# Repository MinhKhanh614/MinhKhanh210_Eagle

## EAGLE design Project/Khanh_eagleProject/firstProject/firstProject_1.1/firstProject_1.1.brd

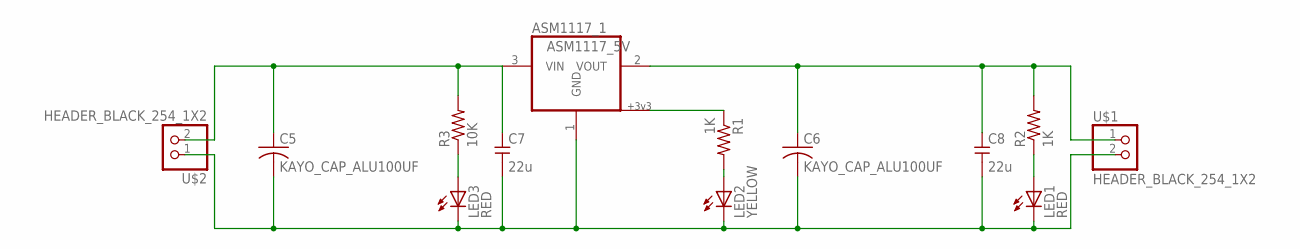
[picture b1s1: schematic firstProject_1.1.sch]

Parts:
ASM1117_1: ASM1117_5V; SOT223
C5, C6: KAYO_CAP_ALU100UF; RCL_PANASONIC_D
C7, C8: 22u; KXN_C0603
LED1, LED3: RED; KXN_LED_0603
LED2: YELLOW; KXN_LED_0603
R1, R2: 1K; R0603_KXN
R3: 10K; R0603_KXN
U$1, U$2: HEADER_BLACK_254_1X2; HEADER_1X2_254

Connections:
GND: ASM1117_1.1 (GND), C5.- (2), C6.- (2), C7.2 (-), C8.2 (-), LED1.C, LED2.C, LED3.C, U$1.2, U$2.1
unnamed: LED3.A, R3.1
unnamed: ASM1117_1.3 (VIN), C5.+ (1), C7.1 (+), R3.2, U$2.2
unnamed: ASM1117_1.2 (VOUT), C6.+ (1), C8.1 (+), R2.2, U$1.1
unnamed: LED2.A, R1.2
unnamed: LED1.A, R2.1
unnamed: ASM1117_1.4, R1.1

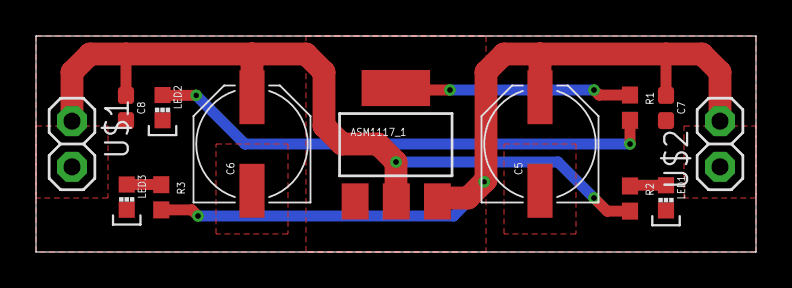
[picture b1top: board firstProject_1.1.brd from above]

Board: 2 copper layers, 40.0 x 12.0 mm, 13 parts (0 on the bottom side), 7 nets.

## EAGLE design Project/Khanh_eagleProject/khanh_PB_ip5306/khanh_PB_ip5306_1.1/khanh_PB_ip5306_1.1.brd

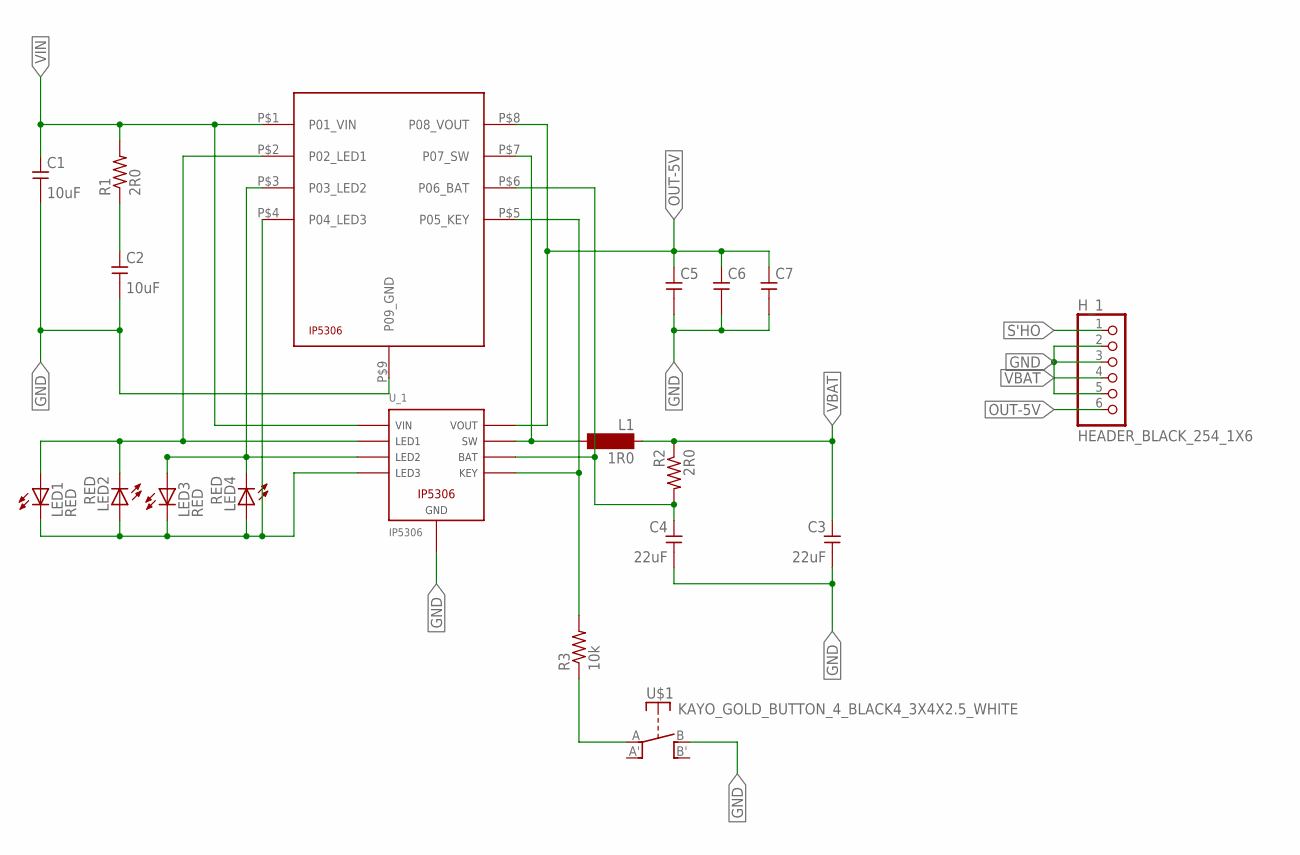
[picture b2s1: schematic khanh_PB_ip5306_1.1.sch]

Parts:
C1, C2: 10uF; C1206
C3, C4: 22uF; C1206
C5, C6, C7: KAYO_CAP_CERAMIC22UF_KXN_0603; KXN_C0603
H_1: HEADER_BLACK_254_1X6; HEADER_1X6_254
L1: 1R0; CKST_0603_0630_PACK
LED1, LED2, LED3, LED4: RED; KXN_LED_0603
R1, R2: 2R0; R0603
R3: 10k; R0603
U$1: KAYO_GOLD_BUTTON_4_BLACK4_3X4X2.5_WHITE; KXN_BUTTON_3_4_2.5MM
U$2: IP5306
U_1: IP5306; ESOP8

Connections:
BAT: C4.1 (+), R2.2, U$2.P$6 (P06_BAT), U_1.6
GND: C1.2 (-), C2.2 (-), C3.2 (-), C4.2 (-), C5.2 (-), C6.2 (-), C7.2 (-), H_1.2, H_1.3, H_1.5, U$1.B, U$2.P$9 (P09_GND), U_1.9
unnamed: C2.1 (+), R1.1
unnamed: R3.1, U$1.A
unnamed: L1.P$2 (2), U$2.P$7 (P07_SW), U_1.7
unnamed: R3.2, U$2.P$5 (P05_KEY), U_1.5
unnamed: LED1.A, LED2.C, U$2.P$2 (P02_LED1), U_1.2
unnamed: LED1.C, LED2.A, LED3.C, LED4.A, U$2.P$4 (P04_LED3), U_1.4
unnamed: LED3.A, LED4.C, U$2.P$3 (P03_LED2), U_1.3
OUT-5V: C5.1 (+), C6.1 (+), C7.1 (+), H_1.6, U$2.P$8 (P08_VOUT), U_1.8
S'HO: H_1.1
VBAT: C3.1 (+), H_1.4, L1.P$1 (1), R2.1
VIN: C1.1 (+), R1.2, U$2.P$1 (P01_VIN), U_1.1

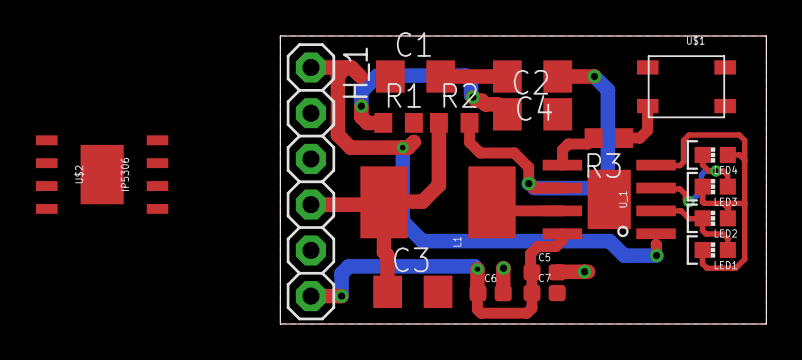
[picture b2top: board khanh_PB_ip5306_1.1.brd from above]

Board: 2 copper layers, 27.0 x 16.0 mm, 19 parts (0 on the bottom side), 12 nets.

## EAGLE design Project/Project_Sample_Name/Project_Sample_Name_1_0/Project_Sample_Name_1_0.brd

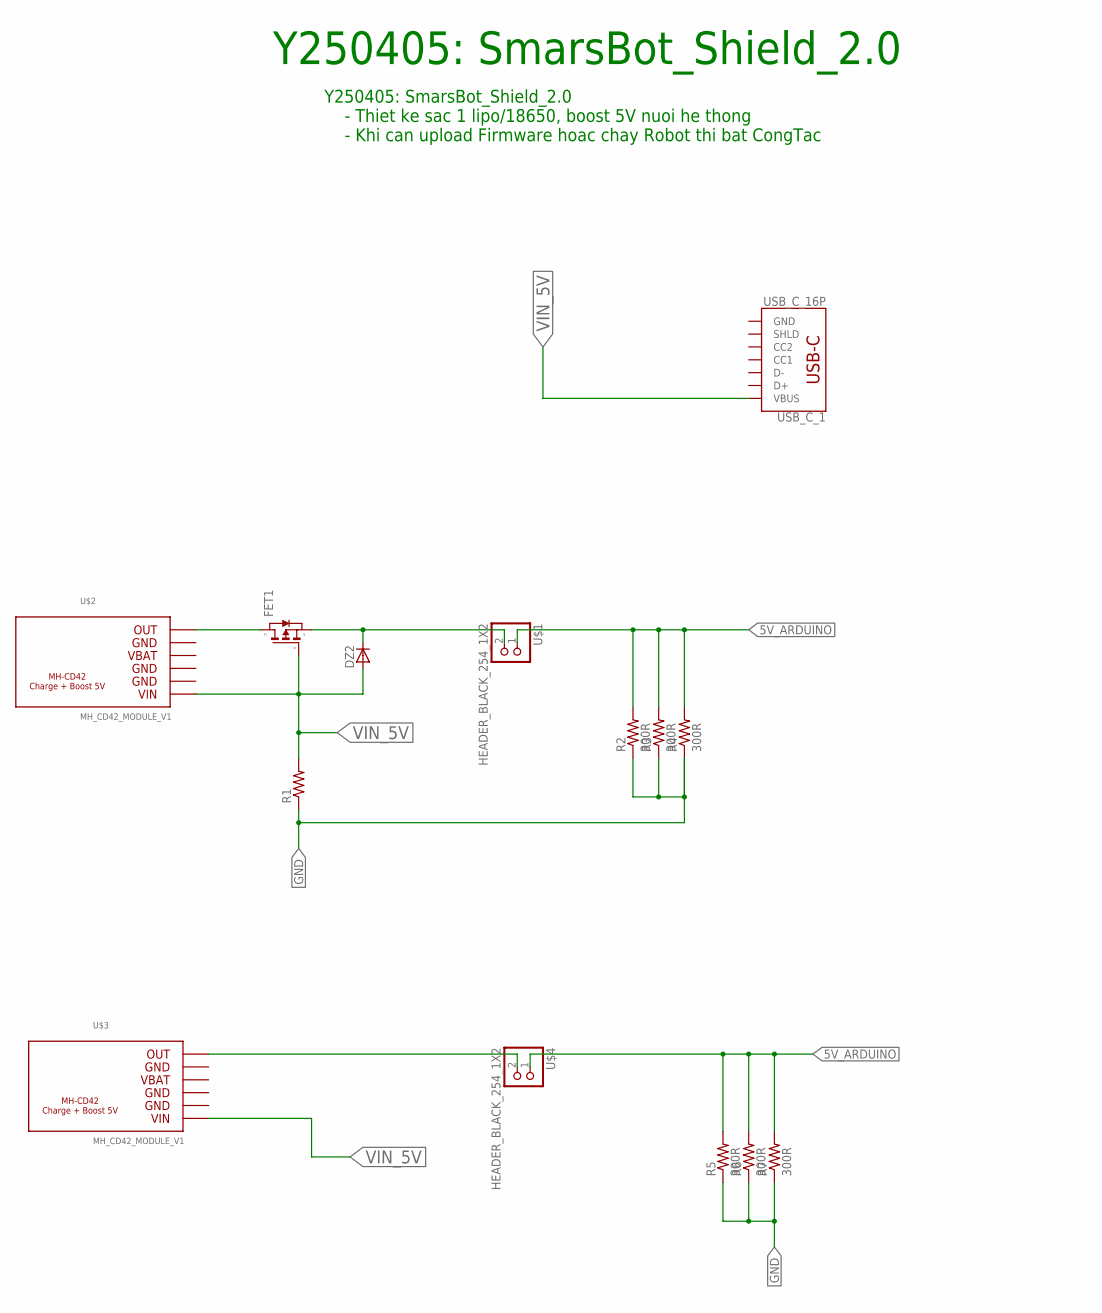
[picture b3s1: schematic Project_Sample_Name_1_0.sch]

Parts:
DZ2: KAYO_DIOD_SS34SMA; SMA
FET1: KAYO_FET_SI2301_SOT23_P; SI2301
R1: R-US_10K_R0603_KXN; R0603_KXN
R2, R3, R4, R5, R6, R7: 300R; R0603_KXN
U$1, U$4: HEADER_BLACK_254_1X2; HEADER_1X2_254_LOCK
U$2, U$3: MH_CD42_MODULE_V1; MODULE_MH_CD42_V1
USB_C_1: USB_C_16P; KXN_SPARKFUN-CONNECTORS_USB-C-16P-2LAYER-PADS

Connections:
5V_ARDUINO: R2.2, R3.2, R4.2, R5.2, R6.2, R7.2, U$1.1, U$4.1
GND: R1.1, R2.1, R3.1, R4.1, R5.1, R6.1, R7.1
unnamed: U$3.6, U$4.2
unnamed: DZ2.C, FET1.S, U$1.2
unnamed: FET1.D, U$2.6
VIN_5V: DZ2.A, FET1.G, R1.2, U$2.1, U$3.1, USB_C_1.VBUS1 (VBUS), USB_C_1.VBUS2 (VBUS)

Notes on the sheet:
Y250405: SmarsBot_Shield_2.0
Y250405: SmarsBot_Shield_2.0 - Thiet ke sac 1 lipo/18650, boost 5V nuoi he thong - Khi can upload Firmware hoac chay Robot thi bat CongTac

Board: 2 copper layers, 14 parts (0 on the bottom side), 6 nets, no tracks yet.

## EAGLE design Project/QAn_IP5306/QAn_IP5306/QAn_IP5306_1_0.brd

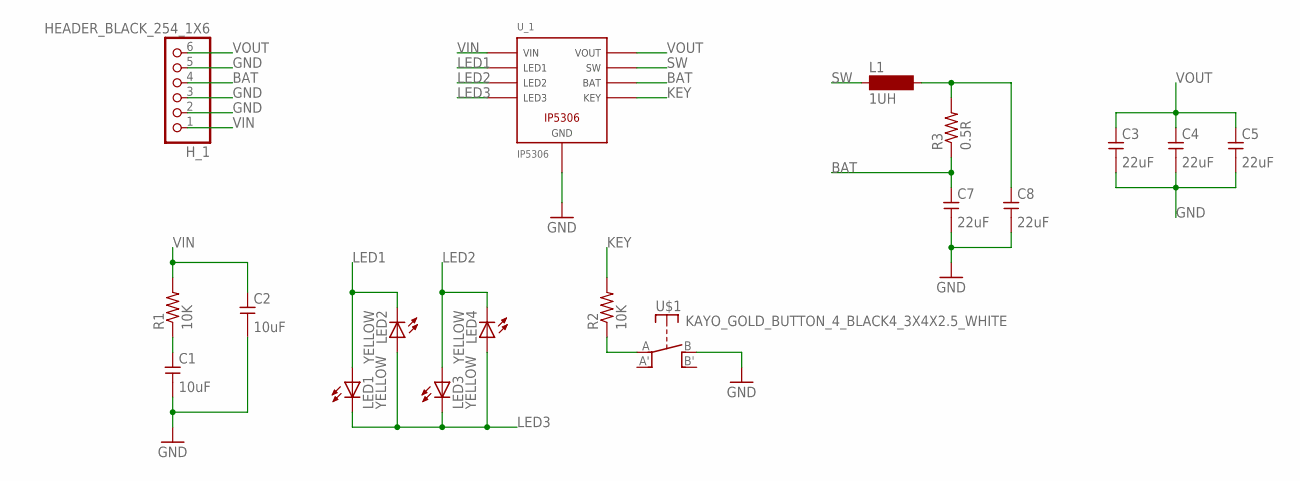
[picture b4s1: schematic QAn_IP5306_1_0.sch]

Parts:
C1, C2: 10uF; C1206
C3, C4, C7, C8: 22uF; C1206
C5: 22uF; KXN_C0603
H_1: HEADER_BLACK_254_1X6; HEADER_1X6_254_LOCK
L1: 1UH; CKST_0603_0630_PACK
LED1, LED2, LED3, LED4: YELLOW; KXN_LED_0603
R1, R2: 10K; R0603_KXN
R3: 0.5R; R0603_KXN
U$1: KAYO_GOLD_BUTTON_4_BLACK4_3X4X2.5_WHITE; KXN_BUTTON_3_4_2.5MM
U_1: IP5306; ESOP8

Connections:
BAT: C7.1 (+), H_1.4, R3.1, U_1.6
GND: C1.2 (-), C2.2 (-), C3.2 (-), C4.2 (-), C5.2 (-), C7.2 (-), C8.2 (-), H_1.2, H_1.3, H_1.5, U$1.B, U_1.9
KEY: R2.2, U_1.5
LED1: LED1.A, LED2.C, U_1.2
LED2: LED3.A, LED4.C, U_1.3
LED3: LED1.C, LED2.A, LED3.C, LED4.A, U_1.4
unnamed: C1.1 (+), R1.1
unnamed: R2.1, U$1.A
unnamed: C8.1 (+), L1.P$2 (2), R3.2
SW: L1.P$1 (1), U_1.7
VIN: C2.1 (+), H_1.1, R1.2, U_1.1
VOUT: C3.1 (+), C4.1 (+), C5.1 (+), H_1.6, U_1.8

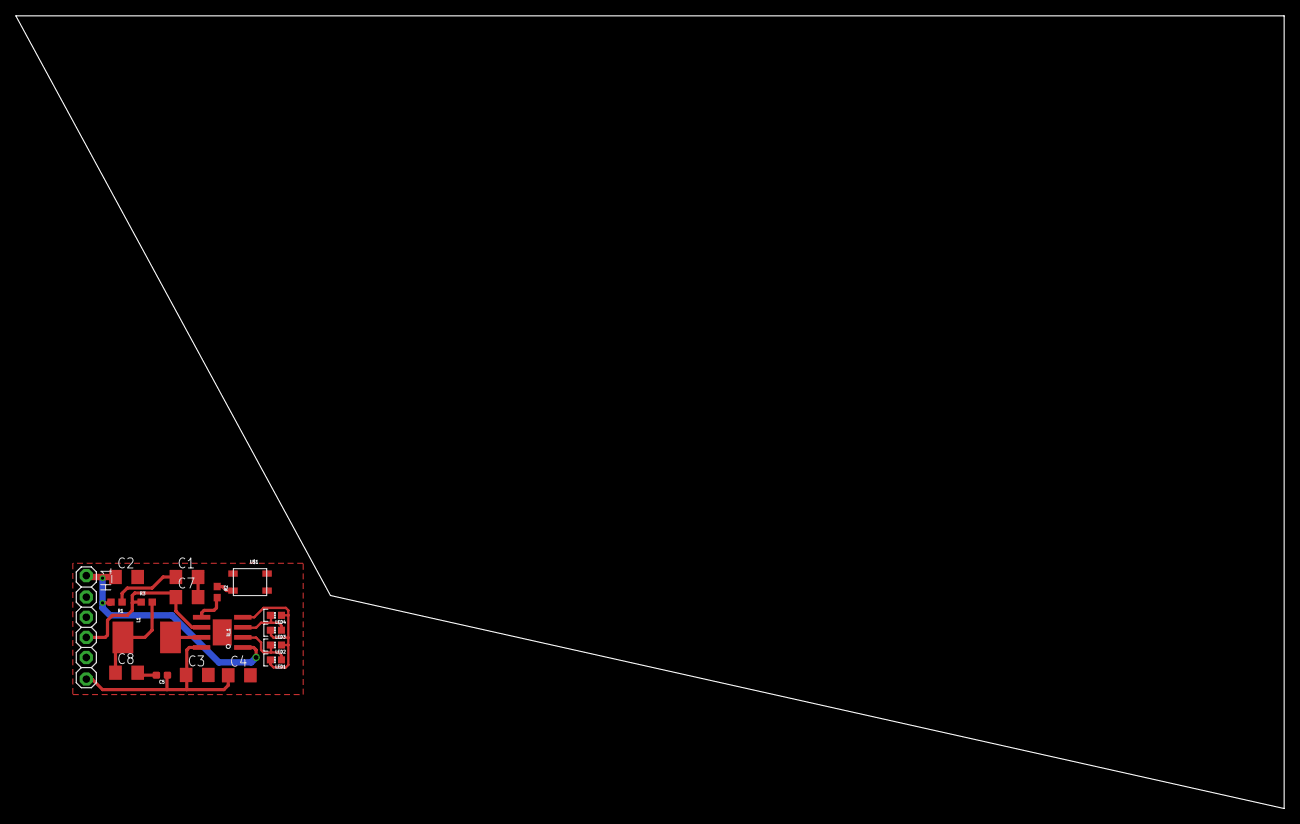
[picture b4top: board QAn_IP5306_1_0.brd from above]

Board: 2 copper layers, 160.0 x 100.0 mm, 18 parts (0 on the bottom side), 12 nets.

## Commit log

2025-06-09 vẽ mạch nguồn 1117 và sạc MH CD
2025-06-09 chỉnh sửa pcd mạch sạc ip5306
2025-06-11 Vẽ Thêm AMS1117 5V v1.1

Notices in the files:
parts and their libraries:
kxnStandard_connector: Licensing: Creative Commons ShareAlike 4.0 International - https://creativecommons.org/licenses/by-sa/4.0
